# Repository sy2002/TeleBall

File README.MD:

TeleBall - Retro Handheld Game Console
======================================

What is TeleBall?
-----------------

TeleBall is a handheld game console. You cannot buy it. You need to build it
by yourself. It lets you play **BreakOut** in single-player mode using one
device and **Tennis for Two** in multi-player mode using two devices 
communicating via radio.

TeleBall is pretty retro and very minimalistic: It features an
8x8 pixel LED matrix display, a paddle as game controller and one button.
Therefore, the range of possible games is limited but you will be surprised
how much fun and even zenlike meditation this kind of gameplay can bring you,
particularly when you play Tennis for Two with a friend.

About this GIT Repository
-------------------------

This repository contains everything you need to build your own TeleBall
device:

* CAD .stl and .cmb.gz data for your 3D printer or for any online 3D print
  shop to 3D print the TeleBall case

* Eagle PCB layout for any online PCB manufacturer to make the TeleBall PCB

* Part lists and hints how to build the hardware

* Arduino source code to flash the firmware

TeleBall is made using the
[Arduino Nano platform](https://store.arduino.cc/arduino-nano) on a
custom PCB.

Browse TeleBall's [project page](http://sy2002.github.io/TeleBall)
for a much better documentation, including a how-to play and
how-to build guide and a bill of materials (BOM). The project page
is also available offline using `index.html` in the root folder of
this repository.

### Folder Structure

    cad:    CAD data for 3D printing the TeleBall case
            Use ".stl" to modify the design or to create a custom output file.
            Most online 3D print shops can use the ".cmb.gz" for production.
            Made with FreeCad: https://FreeCAD.Org

    doc:    HTML documentation; use `index.html` in root folder to browse

    eagle:  Electronic schematic diagram including PCB layout.
            The libraries.zip files are only needed, if you want to modify
            anything; otherwise you can just send the ".brd" file to any
            online PCB manufacturing company to receive a TeleBall PCB.
            Made with the freeware version of Eagle: http://www.cadsoftusa.com

    src:    Arduino source code aka Sketch in the subfolder "TeleBall".
            Compile and upload it to your device using Arduino's IDE. You need
            to install the libraries from libraries.zip first, before being
            able to compile. The "archive" folder contains historic versions.
            Made with Arduino: http://arduino.cc/de/Main/Software

The Makers
----------

TeleBall is brought to you by

* [sy2002](http://www.sy2002.de): idea, code and original circurit design
* doubleflash: additional circurit design and board layout
* lamags: body housing/case

TeleBall was designed, built and released as an Open Source / Open Hardware
project during August 2014 and January 2015.

TeleBall is a project of 
[MEGA - Museum of Electronic Games & Art](http://www.m-e-g-a.org/diy-teleball/).

We are looking forward to hearing from you. Email to sy2002 at teleball.org

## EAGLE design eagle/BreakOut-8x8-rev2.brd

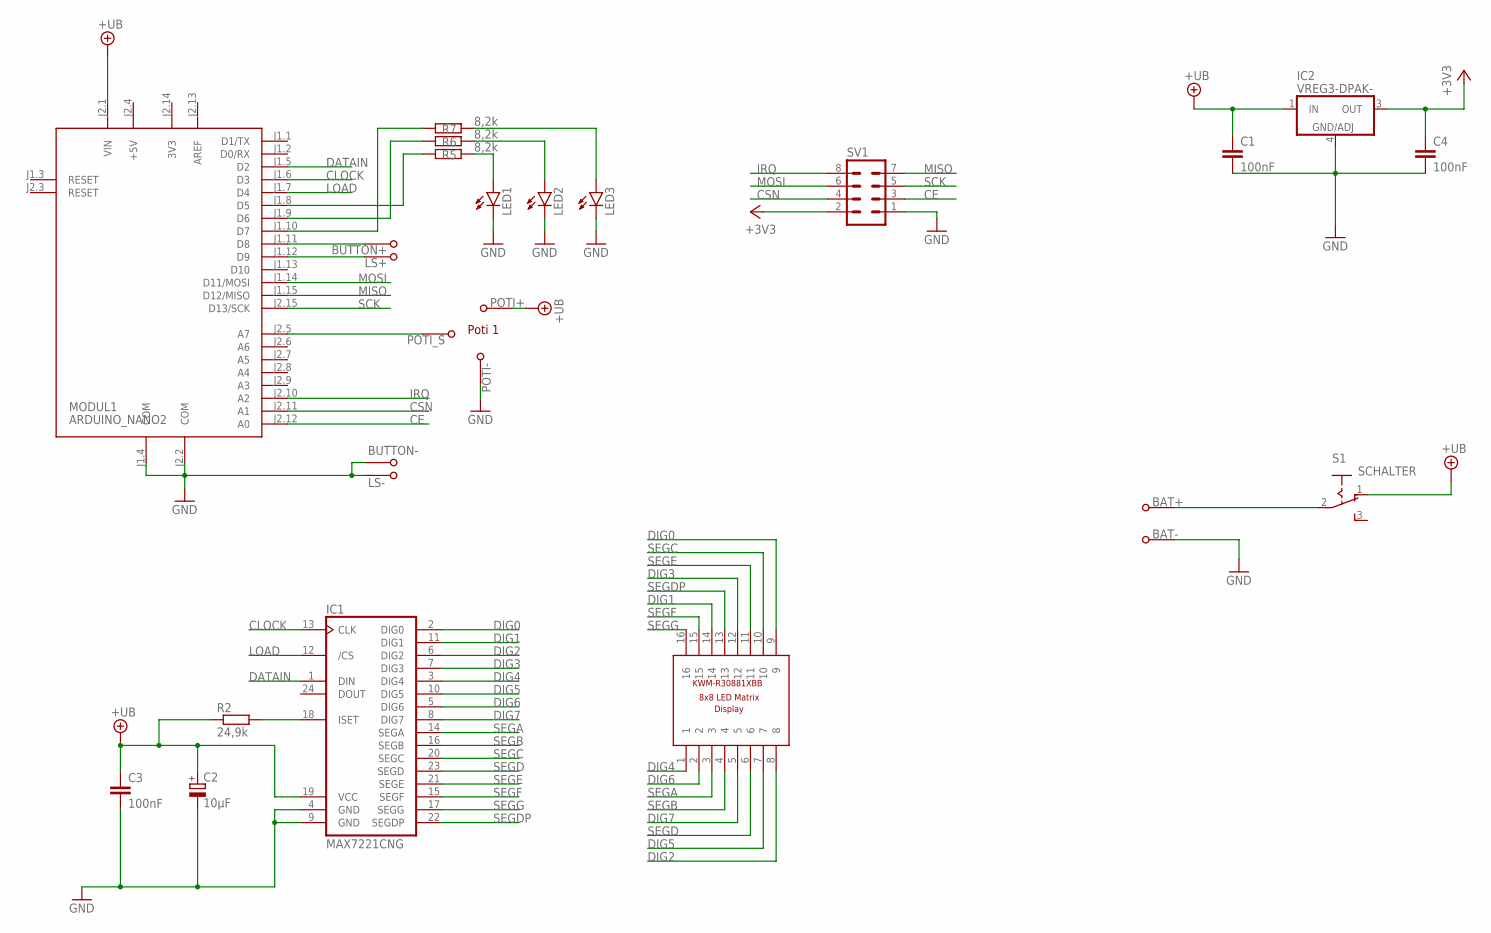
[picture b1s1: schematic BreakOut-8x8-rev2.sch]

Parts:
BAT+: PAD-NVSMD-2X3; PAD-SO-2X3
BAT-: PAD-NVSMD-2X3; PAD-SO-2X3
BUTTON+: PAD-NVSMD-2X3; PAD-SO-2X3
BUTTON-: PAD-NVSMD-2X3; PAD-SO-2X3
C1, C3, C4: 100nF; C0805
C2: 10µF; C/6032-28R
IC1: MAX7221CNG; DIL24-3
IC2: VREG3-DPAK-; DPAK
LED1, LED2, LED3: LED5MM
LS+: PAD-NVSMD-2X3; PAD-SO-2X3
LS-: PAD-NVSMD-2X3; PAD-SO-2X3
MODUL1: ARDUINO_NANO2
POTI+: PAD-NVSMD-2X3; PAD-SO-2X3
POTI-: PAD-NVSMD-2X3; PAD-SO-2X3
POTI_S: PAD-NVSMD-2X3; PAD-SO-2X3
R2: 24,9k; R0805
R5, R6, R7: 8,2k; R0805
S1: SCHALTER; 255SB
SV1: MA04-2
U$1: KWM-R30881XBB

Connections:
3V3: MODUL1.J2.14 (3V3)
+3V3: C4.1, IC2.3 (OUT), SV1.2
+5V: MODUL1.J2.4 (+5V)
+UB: C1.1, C2.+, C3.1, IC1.19 (VCC), IC2.1 (IN), MODUL1.J2.1 (VIN), POTI+.1, R2.1, S1.1
AREF: MODUL1.J2.13 (AREF)
BUTTON: MODUL1.J1.10 (D7), R7.1
CE: MODUL1.J2.12 (A0), SV1.3
CLOCK: IC1.13 (CLK), MODUL1.J1.6 (D3)
CSN: MODUL1.J2.11 (A1), SV1.4
DATAIN: IC1.1 (DIN), MODUL1.J1.5 (D2)
DIG0: IC1.2 (DIG0), U$1.9
DIG1: IC1.11 (DIG1), U$1.14
DIG2: IC1.6 (DIG2), U$1.8
DIG3: IC1.7 (DIG3), U$1.12
DIG4: IC1.3 (DIG4), U$1.1
DIG5: IC1.10 (DIG5), U$1.7
DIG6: IC1.5 (DIG6), U$1.2
DIG7: IC1.8 (DIG7), U$1.5
GND: BAT-.1, BUTTON-.1, C1.2, C2.-, C3.2, C4.2, IC1.4 (GND), IC1.9 (GND), IC2.4 (GND/ADJ), LED1.K (C), LED2.K (C), LED3.K (C), LS-.1, MODUL1.J1.4 (COM), MODUL1.J2.2 (COM), POTI-.1, SV1.1
IRQ: MODUL1.J2.10 (A2), SV1.8
LOAD: IC1.12 (/CS), MODUL1.J1.7 (D4)
MISO: MODUL1.J1.15 (D12/MISO), SV1.7
MOSI: MODUL1.J1.14 (D11/MOSI), SV1.6
unnamed: BUTTON+.1, MODUL1.J1.11 (D8)
unnamed: LED1.A, R5.2
unnamed: LED2.A, R6.2
unnamed: LED3.A, R7.2
unnamed: MODUL1.J2.5 (A7), POTI_S.1
unnamed: BAT+.1, S1.2
unnamed: LS+.1, MODUL1.J1.12 (D9)
unnamed: IC1.18 (ISET), R2.2
unnamed: MODUL1.J1.9 (D6), R6.1
unnamed: MODUL1.J1.8 (D5), R5.1
SCK: MODUL1.J2.15 (D13/SCK), SV1.5
SEGA: IC1.14 (SEGA), U$1.3
SEGB: IC1.16 (SEGB), U$1.4
SEGC: IC1.20 (SEGC), U$1.10
SEGD: IC1.23 (SEGD), U$1.6
SEGDP: IC1.22 (SEGDP), U$1.13
SEGE: IC1.21 (SEGE), U$1.11
SEGF: IC1.15 (SEGF), U$1.15
SEGG: IC1.17 (SEGG), U$1.16

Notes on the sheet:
Poti 1

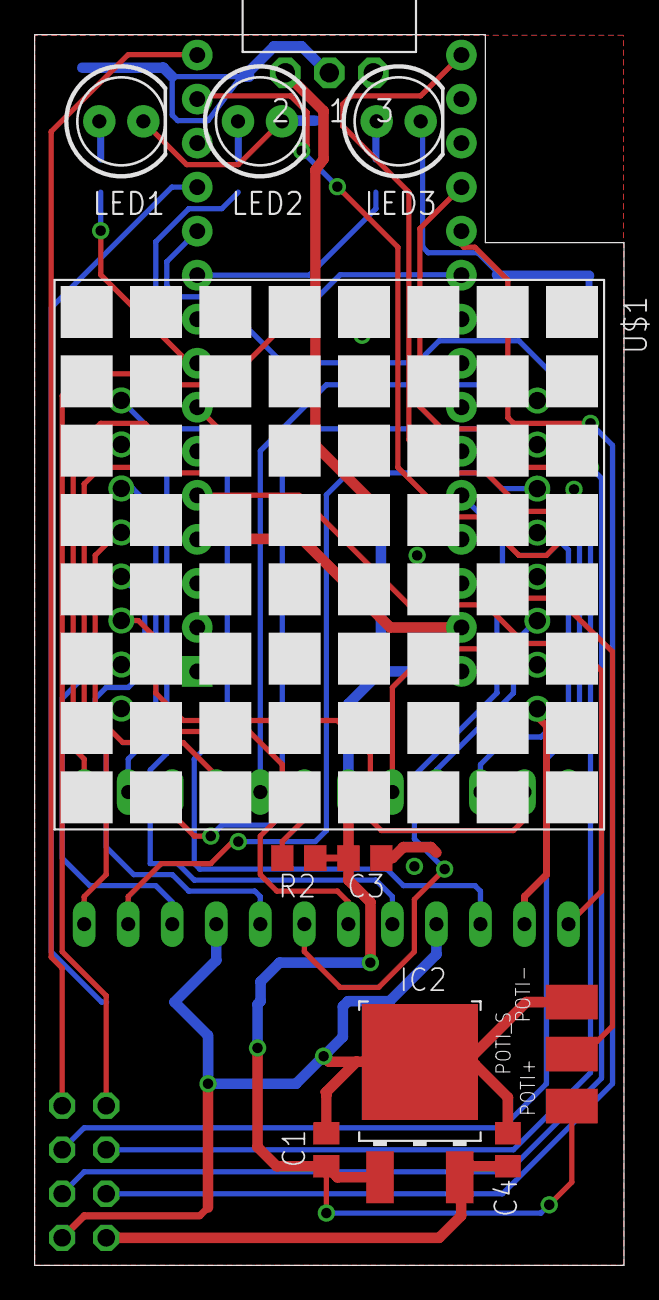
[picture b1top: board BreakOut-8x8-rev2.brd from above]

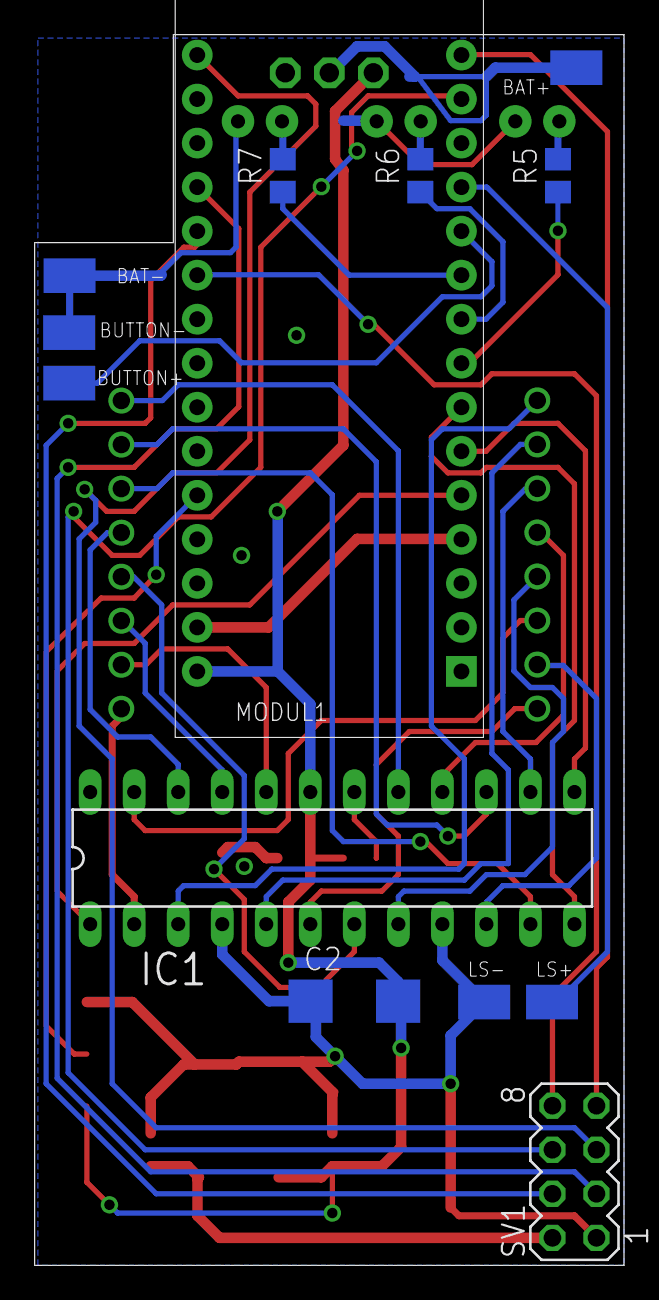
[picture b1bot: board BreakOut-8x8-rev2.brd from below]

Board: 2 copper layers, 34.0 x 71.0 mm, 26 parts (13 on the bottom side), 39 nets.

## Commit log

2014-12-26 GIT repo created and V1.1 files added
2014-12-26 bugfixes: tennis, pairing, eeprom selector
2014-12-30 bugfixes, SRAM optimization, menu changes
2014-12-30 bugfixes
2014-12-30 final bugfixes for V1.2 release
2015-01-01 changed various timing constants and added illustrations
2015-01-01 preparations for GITHUB
2015-01-01 License and README.MD
2015-01-01 wip documentation
2015-01-01 Create gh-pages branch via GitHub
2015-01-01 wip pages and documentation
2015-01-02 documentation and pages
2015-01-02 pages and documentation
2015-01-03 wip documentation and pages
2015-01-07 adding google analytics
2015-01-07 CNAME file for custom domain
2015-01-08 moved Levels constant to a more suitable place
2015-01-09 final documentation and pages
2015-01-09 final V1.2 packaging including documentation
2015-01-19 Update software.md
    corrected a typo
2016-05-27 wip resolve GitHub Pages display bug: delete CNAME as an attempt to break circular referencing
2016-05-27 wip resolve GitHub Pages display problem
2016-05-27 wip resolving GitHub Pages display problem
2016-05-28 wip resolving GitHub Pages display issues
2016-05-28 wip resolve GitHub Pages display issues
2016-05-28 resolved GitHub Pages display issues (which were some strange DNS / redirect / looping issues either on the side of GitHub or on 1und1.de)
2016-06-03 BOM update
2019-04-22 doc and website links and fontsize updated
2019-08-20 https for YouTube links
2025-07-01 Updated FreeCAD address.

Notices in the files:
parts and their libraries:
SparkFun-LED: Licensing: Creative Commons ShareAlike 4.0 International - https://creativecommons.org/licenses/by-sa/4.0
